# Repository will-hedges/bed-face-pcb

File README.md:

# bed-face-pcb
An open-source 4x12 ortholinear keyboard based on the Pro Micro / nice!nano

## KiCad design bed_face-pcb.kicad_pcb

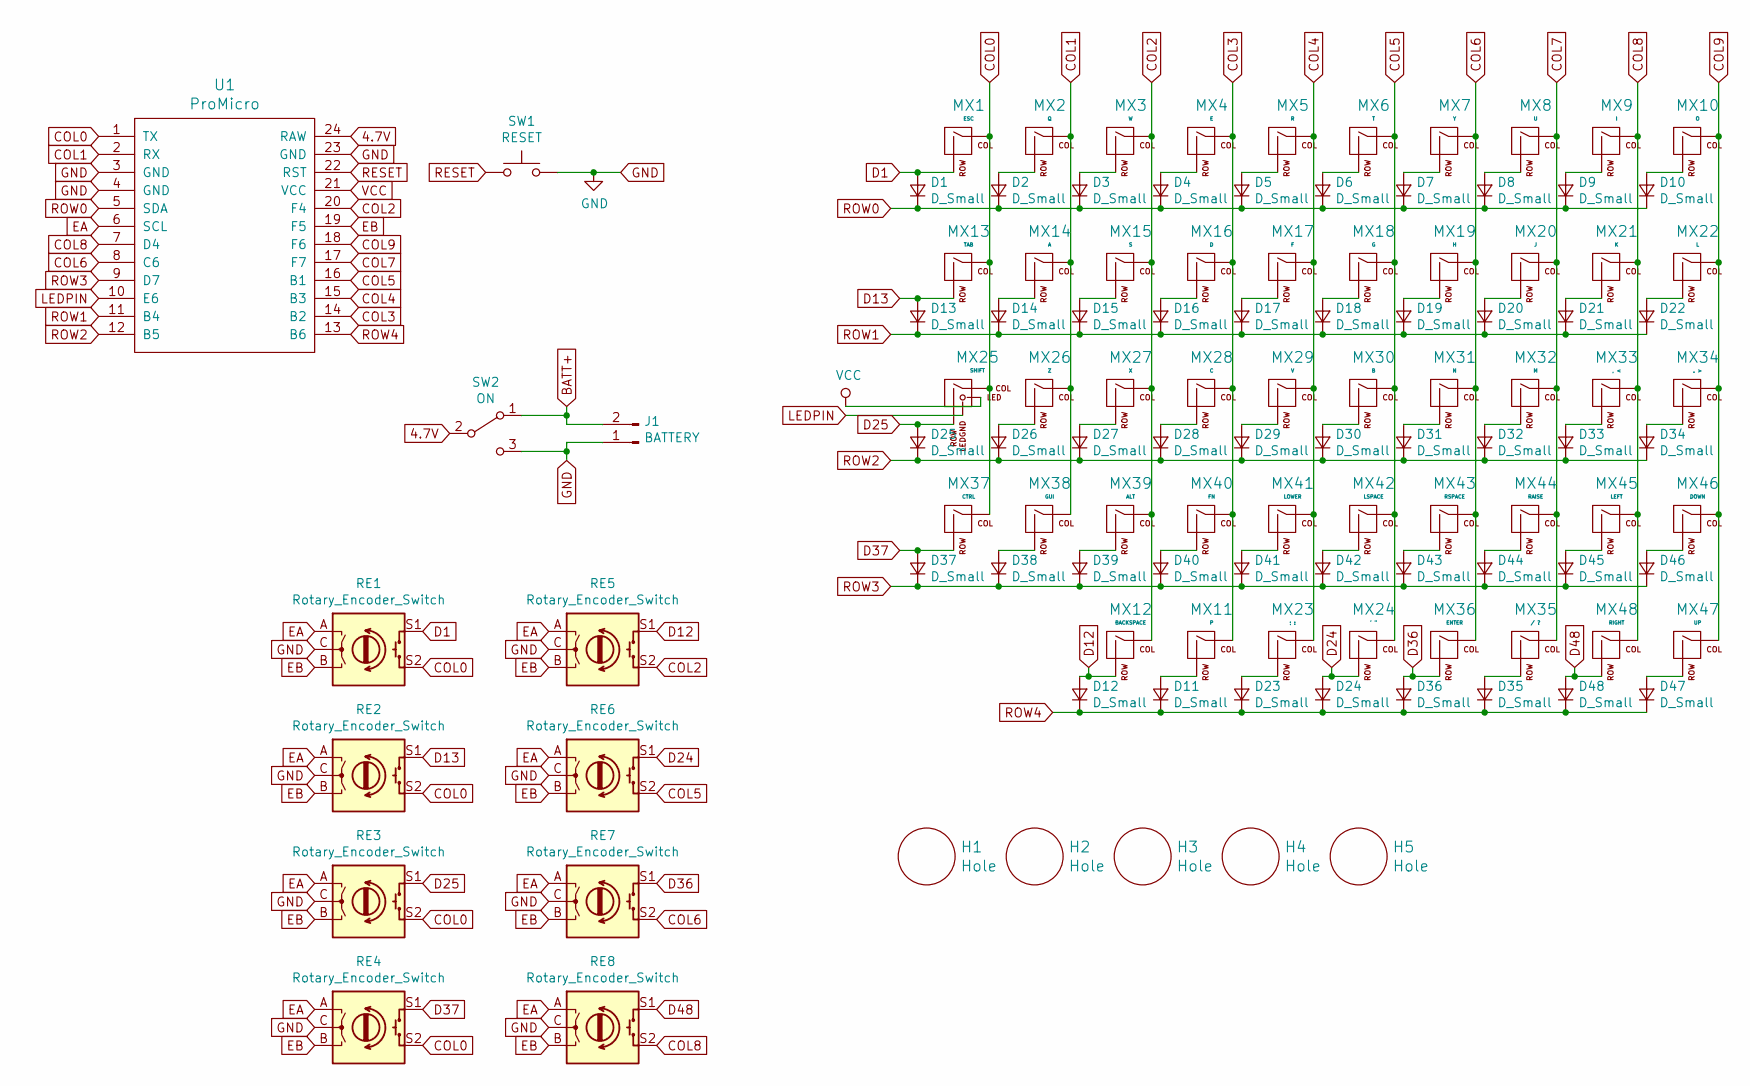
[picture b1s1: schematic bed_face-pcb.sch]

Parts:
D1, D2, D3, D4, D5, D6, D7, D8, D9, D10, D11, D12, D13, D14, D15, D16, D17, D18, D19, D20, D21, D22, D23, D24, D25, D26, D27, D28, D29, D30, D31, D32, D33, D34, D35, D36, D37, D38, D39, D40, D41, D42, D43, D44, D45, D46, D47, D48: D_Small; Diode-Hybrid-Back-EDIT
H1, H2, H3, H4, H5: Hole; standoff_hole
J1: BATTERY; JST_PH_S2B-PH-K_1x02_P2.00mm_Horizontal
MX1: ESC; MXOnly-1U-NoLED-EDIT
MX2: Q; MXOnly-1U-NoLED-EDIT
MX3: W; MXOnly-1U-NoLED-EDIT
MX4: E; MXOnly-1U-NoLED-EDIT
MX5: R; MXOnly-1U-NoLED-EDIT
MX6: T; MXOnly-1U-NoLED-EDIT
MX7: Y; MXOnly-1U-NoLED-EDIT
MX8: U; MXOnly-1U-NoLED-EDIT
MX9: I; MXOnly-1U-NoLED-EDIT
MX10: O; MXOnly-1U-NoLED-EDIT
MX11: P; MXOnly-1U-NoLED-EDIT
MX12: BACKSPACE; MXOnly-1U-NoLED-EDIT
MX13: TAB; MXOnly-1U-NoLED-EDIT
MX14: A; MXOnly-1U-NoLED-EDIT
MX15: S; MXOnly-1U-NoLED-EDIT
MX16: D; MXOnly-1U-NoLED-EDIT
MX17: F; MXOnly-1U-NoLED-EDIT
MX18: G; MXOnly-1U-NoLED-EDIT
MX19: H; MXOnly-1U-NoLED-EDIT
MX20: J; MXOnly-1U-NoLED-EDIT
MX21: K; MXOnly-1U-NoLED-EDIT
MX22: L; MXOnly-1U-NoLED-EDIT
MX23: ; :; MXOnly-1U-NoLED-EDIT
MX24: ' \"; MXOnly-1U-NoLED-EDIT
MX25: SHIFT; MXOnly-1U-EDIT
MX26: Z; MXOnly-1U-NoLED-EDIT
MX27: X; MXOnly-1U-NoLED-EDIT
MX28: C; MXOnly-1U-NoLED-EDIT
MX29: V; MXOnly-1U-NoLED-EDIT
MX30: B; MXOnly-1U-NoLED-EDIT
MX31: N; MXOnly-1U-NoLED-EDIT
MX32: M; MXOnly-1U-NoLED-EDIT
MX33: , <; MXOnly-1U-NoLED-EDIT
MX34: . >; MXOnly-1U-NoLED-EDIT
MX35: / ?; MXOnly-1U-NoLED-EDIT
MX36: ENTER; MXOnly-1U-NoLED-EDIT
MX37: CTRL; MXOnly-1U-NoLED-EDIT
MX38: GUI; MXOnly-1U-NoLED-EDIT
MX39: ALT; MXOnly-1U-NoLED-EDIT
MX40: FN; MXOnly-1U-NoLED-EDIT
MX41: LOWER; MXOnly-1U-2U-EDIT-LOWER
MX42: LSPACE; MXOnly-2U-ReversedStabilizers-NoLED-ComboSpace-EDIT
MX43: RSPACE; MXOnly-1U-NoLED-EDIT-No-Corners
MX44: RAISE; MXOnly-1U-2U-EDIT-RAISE
MX45: LEFT; MXOnly-1U-NoLED-EDIT
MX46: DOWN; MXOnly-1U-NoLED-EDIT
MX47: UP; MXOnly-1U-NoLED-EDIT
MX48: RIGHT; MXOnly-1U-NoLED-EDIT
RE1, RE2, RE3, RE4, RE5, RE6, RE7, RE8: Rotary_Encoder_Switch; EC11_Switch-EDIT
SW1: RESET; SKQG-1155865
SW2: ON; SWITCH_SPST_SMD_A-EDIT
U1: ProMicro; ArduinoProMicro-BackSide

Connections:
4.7V: SW2.2 (B), U1.24 (RAW)
BATT+: J1.2, SW2.1 (A)
COL0: MX1.1 (COL), MX13.1 (COL), MX25.1 (COL), MX37.1 (COL), RE1.S2, RE2.S2, RE3.S2, RE4.S2, U1.1 (TX)
COL1: MX2.1 (COL), MX14.1 (COL), MX26.1 (COL), MX38.1 (COL), U1.2 (RX)
COL2: MX3.1 (COL), MX12.1 (COL), MX15.1 (COL), MX27.1 (COL), MX39.1 (COL), RE5.S2, U1.20 (F4)
COL3: MX4.1 (COL), MX11.1 (COL), MX16.1 (COL), MX28.1 (COL), MX40.1 (COL), U1.14 (B2)
COL4: MX5.1 (COL), MX17.1 (COL), MX23.1 (COL), MX29.1 (COL), MX41.1 (COL), U1.15 (B3)
COL5: MX6.1 (COL), MX18.1 (COL), MX24.1 (COL), MX30.1 (COL), MX42.1 (COL), RE6.S2, U1.16 (B1)
COL6: MX7.1 (COL), MX19.1 (COL), MX31.1 (COL), MX36.1 (COL), MX43.1 (COL), RE7.S2, U1.8 (C6)
COL7: MX8.1 (COL), MX20.1 (COL), MX32.1 (COL), MX35.1 (COL), MX44.1 (COL), U1.17 (F7)
COL8: MX9.1 (COL), MX21.1 (COL), MX33.1 (COL), MX45.1 (COL), MX48.1 (COL), RE8.S2, U1.7 (D4)
COL9: MX10.1 (COL), MX22.1 (COL), MX34.1 (COL), MX46.1 (COL), MX47.1 (COL), U1.18 (F6)
D1: D1.2 (A), MX1.2 (ROW), RE1.S1
D12: D12.2 (A), MX12.2 (ROW), RE5.S1
D13: D13.2 (A), MX13.2 (ROW), RE2.S1
D24: D24.2 (A), MX24.2 (ROW), RE6.S1
D25: D25.2 (A), MX25.2 (ROW), RE3.S1
D36: D36.2 (A), MX36.2 (ROW), RE7.S1
D37: D37.2 (A), MX37.2 (ROW), RE4.S1
D48: D48.2 (A), MX48.2 (ROW), RE8.S1
EA: RE1.A, RE2.A, RE3.A, RE4.A, RE5.A, RE6.A, RE7.A, RE8.A, U1.6 (SCL)
EB: RE1.B, RE2.B, RE3.B, RE4.B, RE5.B, RE6.B, RE7.B, RE8.B, U1.19 (F5)
GND: J1.1, RE1.C, RE2.C, RE3.C, RE4.C, RE5.C, RE6.C, RE7.C, RE8.C, SW1.2, SW2.3 (C), U1.3 (GND), U1.4 (GND), U1.23 (GND)
LEDPIN: MX25.4 (LEDGND), U1.10 (E6)
unnamed: D2.2 (A), MX2.2 (ROW)
unnamed: D3.2 (A), MX3.2 (ROW)
unnamed: D4.2 (A), MX4.2 (ROW)
unnamed: D5.2 (A), MX5.2 (ROW)
unnamed: D6.2 (A), MX6.2 (ROW)
unnamed: D7.2 (A), MX7.2 (ROW)
unnamed: D8.2 (A), MX8.2 (ROW)
unnamed: D9.2 (A), MX9.2 (ROW)
unnamed: D10.2 (A), MX10.2 (ROW)
unnamed: D11.2 (A), MX11.2 (ROW)
unnamed: D14.2 (A), MX14.2 (ROW)
unnamed: D15.2 (A), MX15.2 (ROW)
unnamed: D16.2 (A), MX16.2 (ROW)
unnamed: D17.2 (A), MX17.2 (ROW)
unnamed: D18.2 (A), MX18.2 (ROW)
unnamed: D19.2 (A), MX19.2 (ROW)
unnamed: D20.2 (A), MX20.2 (ROW)
unnamed: D21.2 (A), MX21.2 (ROW)
unnamed: D22.2 (A), MX22.2 (ROW)
unnamed: D23.2 (A), MX23.2 (ROW)
unnamed: D26.2 (A), MX26.2 (ROW)
unnamed: D27.2 (A), MX27.2 (ROW)
unnamed: D28.2 (A), MX28.2 (ROW)
unnamed: D29.2 (A), MX29.2 (ROW)
unnamed: D30.2 (A), MX30.2 (ROW)
unnamed: D31.2 (A), MX31.2 (ROW)
unnamed: D32.2 (A), MX32.2 (ROW)
unnamed: D33.2 (A), MX33.2 (ROW)
unnamed: D34.2 (A), MX34.2 (ROW)
unnamed: D35.2 (A), MX35.2 (ROW)
unnamed: D38.2 (A), MX38.2 (ROW)
unnamed: D39.2 (A), MX39.2 (ROW)
unnamed: D40.2 (A), MX40.2 (ROW)
unnamed: D41.2 (A), MX41.2 (ROW)
unnamed: D42.2 (A), MX42.2 (ROW)
unnamed: D43.2 (A), MX43.2 (ROW)
unnamed: D44.2 (A), MX44.2 (ROW)
unnamed: D45.2 (A), MX45.2 (ROW)
unnamed: D46.2 (A), MX46.2 (ROW)
unnamed: D47.2 (A), MX47.2 (ROW)
RESET: SW1.1, U1.22 (RST)
ROW0: D1.1 (K), D2.1 (K), D3.1 (K), D4.1 (K), D5.1 (K), D6.1 (K), D7.1 (K), D8.1 (K), D9.1 (K), D10.1 (K), U1.5 (SDA)
ROW1: D13.1 (K), D14.1 (K), D15.1 (K), D16.1 (K), D17.1 (K), D18.1 (K), D19.1 (K), D20.1 (K), D21.1 (K), D22.1 (K), U1.11 (B4)
ROW2: D25.1 (K), D26.1 (K), D27.1 (K), D28.1 (K), D29.1 (K), D30.1 (K), D31.1 (K), D32.1 (K), D33.1 (K), D34.1 (K), U1.12 (B5)
ROW3: D37.1 (K), D38.1 (K), D39.1 (K), D40.1 (K), D41.1 (K), D42.1 (K), D43.1 (K), D44.1 (K), D45.1 (K), D46.1 (K), U1.9 (D7)
ROW4: D11.1 (K), D12.1 (K), D23.1 (K), D24.1 (K), D35.1 (K), D36.1 (K), D47.1 (K), D48.1 (K), U1.13 (B6)
VCC: MX25.3 (LED), U1.21 (VCC)

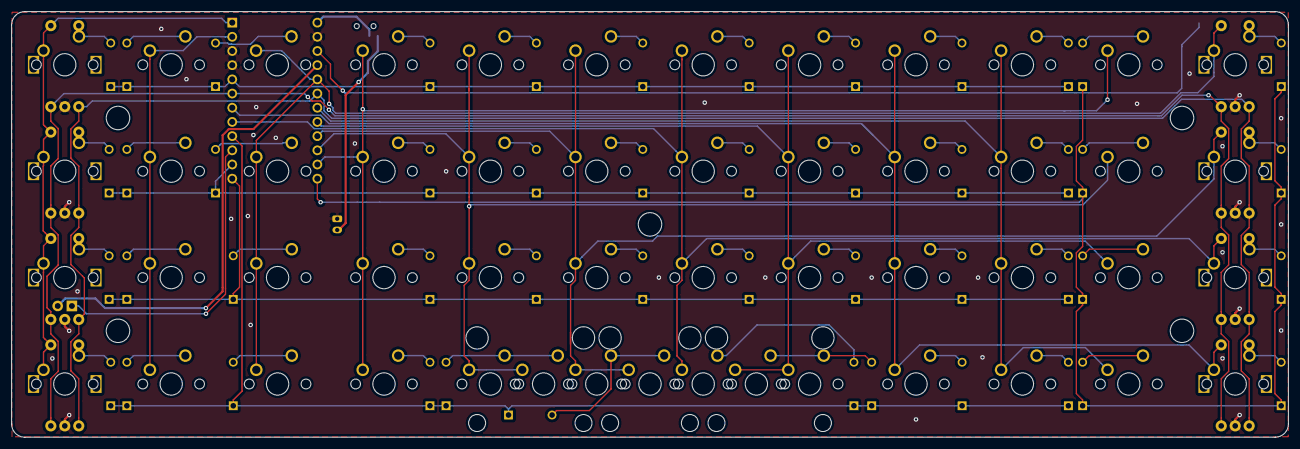
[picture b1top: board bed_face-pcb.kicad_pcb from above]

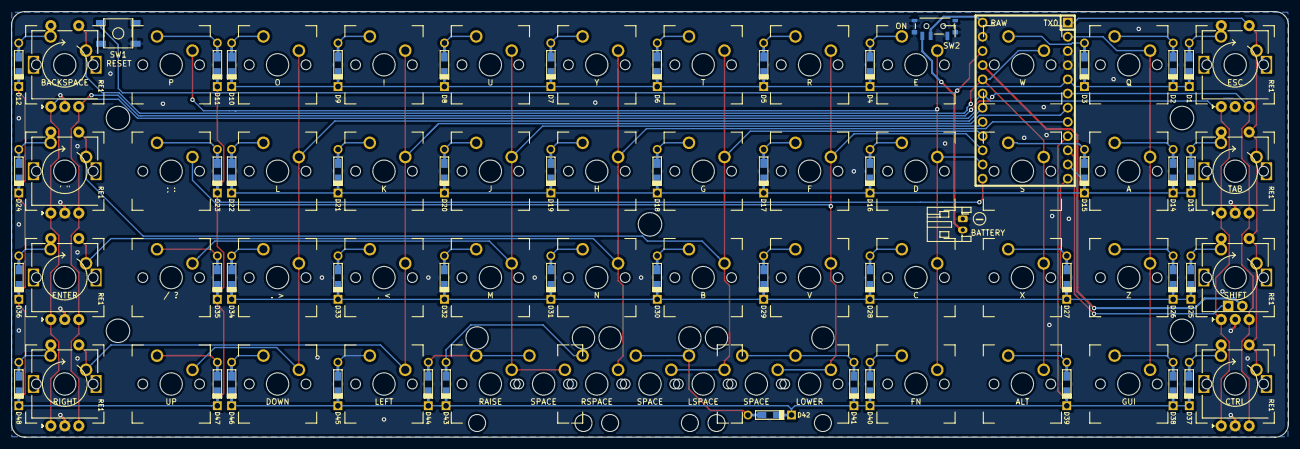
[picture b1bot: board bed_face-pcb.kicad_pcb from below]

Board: 2 copper layers, 228.6 x 76.2 mm, 113 parts (3 on the bottom side), 71 nets.

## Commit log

2023-05-23 project initialized
2023-05-23 added submodules
2023-05-23 updated symbol libraries
2023-05-23 added ProMicro submodule, libraries
2023-05-23 initial matrix
2023-05-23 added Keebio Parts submodule
2023-05-23 re-ordered annotations, begain placing components
2023-05-23 keys placed * may change to my personal layout
2023-05-23 styled switch footprints, initial pcb placement
2023-05-24 added +5V, GND to Power net w/ 15 mil track width
2023-05-25 matrix routed, GND fill placed * still needs resistor for LED? * need to add silkscreen/graphic
2023-06-03 added split vs. 2u space
2023-06-04 began placing encoders, squaring matrix * squaring matrix gains MCU pins * RE footpints need silkscreen changes
2023-06-05 squared up matrix, placed + tracked encoders * encoder support for first and last columns * needs battery connector * encoder silks need changing
2023-06-05 improved GND fill after encoder placement/tracks
2023-06-10 added encoder spots, mounting holes, moved pro micro * standard mount holes interfered with pro micro * rewired after moving, changed some pins * fixed space footprint * began moving used footprints 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
2023-06-10 added pads to f.mask, changed footprint silks, make SW1 th
2023-06-11 added miniature power switch * TODO closely check power pinout
2023-11-07 finished tracking
